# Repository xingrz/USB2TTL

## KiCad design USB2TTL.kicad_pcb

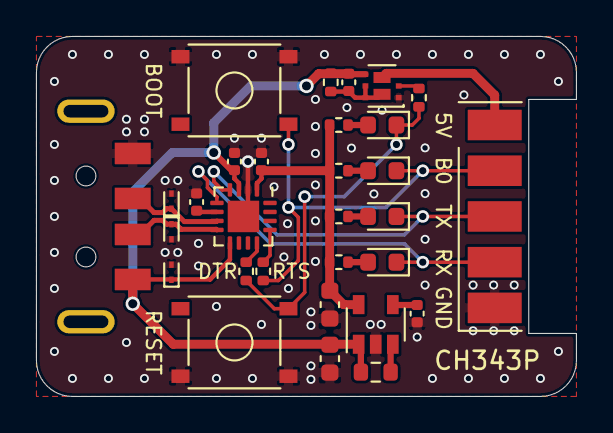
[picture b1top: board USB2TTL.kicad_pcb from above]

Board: 2 copper layers, 30.0 x 20.0 mm, 30 parts (0 on the bottom side), 21 nets.

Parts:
C1, C3: 10uF/25V; C_0603_1608Metric
C2: 10nF; C_0402_1005Metric
C4, C5, C6, C7: 0.1uF; C_0402_1005Metric
D1, D2, D3: LESD5Z5.0CT1G; D_SOD-923
D4, D5, D6, D7: LED; LED_0603_1608Metric
J1: USB_A; MOLEX_48037-2200
J2: Conn_01x05; PinHeader_1x05_P2.54mm_Horizontal_SMD
Q1: SiA517DJ; Vishay_PowerPAK_SC70-6L_Dual
R1: 10K; R_0603_1608Metric
R2: 1K; R_0402_1005Metric
R3: 100R; R_0402_1005Metric
R4, R5, R6, R7: 4.7K; R_0402_1005Metric
R8, R9: 0R; R_0402_1005Metric
SW1, SW2: TS-1187A-B-A-B; XKB_TS-1187A-B-A-B
U1: SPX3819M5-L-3-3; SOT-23-5
U2: CH343P; WQFN-16-1EP_3x3mm_P0.5mm_EP1.75x1.75mm

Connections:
+3V3: C3.1, C7.1, R4.2, R5.2, R6.2, R7.2, U1.5, U2.1
+5V: C1.1, C4.1, C6.1, D3.1, J1.1, Q1.4, R1.2, R2.1, U1.1, U2.3, U2.9
/BOOT: D6.1, J2.2, R9.1, SW2.1
/D+: D2.1, J1.3, U2.7
/D-: D1.1, J1.2, U2.8
/DTR: R8.2, U2.12
/RESET: D7.1, R3.2, R8.1, SW1.1
/RTS: R9.2, U2.13
/RXD: D5.1, J2.4, U2.5
/TXD: D4.1, J2.3, U2.4
/VOUT: J2.1, Q1.3
GND: C1.2, C2.2, C3.2, C5.2, C6.2, C7.2, D1.2, D2.2, D3.2, J1.4, J2.5, Q1.1, SW1.2, SW2.2, U1.2, U2.2, U2.17
unnamed: C2.1, U1.4
unnamed: C4.2, Q1.5, Q1.6, R2.2
unnamed: C5.1, U2.6
unnamed: D4.2, R4.1
unnamed: D5.2, R5.1
unnamed: D6.2, R6.1
unnamed: D7.2, R7.1
unnamed: Q1.2, R3.1
unnamed: R1.1, U1.3

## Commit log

2022-05-25 Init repository
2022-05-25 Basic set up
2022-05-25 Done V1.0
2022-05-25 Output gerber
2022-06-01 Fix rotation of SiA517DJ
